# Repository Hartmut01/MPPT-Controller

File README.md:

# MPPT-Controller
#

bla bla bla

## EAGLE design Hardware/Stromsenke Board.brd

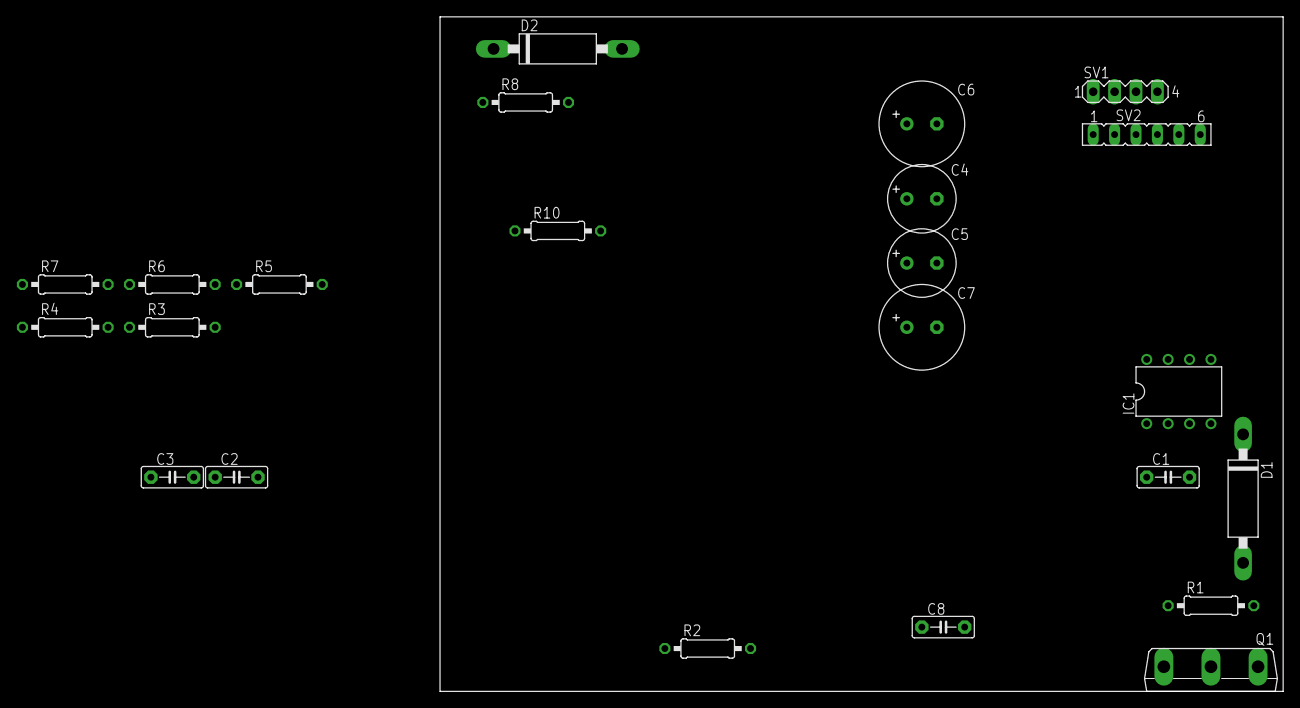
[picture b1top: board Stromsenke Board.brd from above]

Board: 2 copper layers, 100.0 x 80.0 mm, 23 parts (0 on the bottom side), 15 nets, no tracks yet.

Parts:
C1, C2, C3, C8: 100n; C5B2.5
C4, C5: E3,5-8
C6, C7: E3,5-10
D1: 8,7V; C1702-15
D2: 5v; C1702-15
IC1: LM358N; DIL08
Q1: IRFPC40; TO247BV
R1, R7: 1k; 0207/10
R2: 0R1; 0207/10
R3: 2k7; 0207/10
R4: 330R; 0207/10
R5: 10k; 0207/10
R6: 3k3; 0207/10
R8: 670R; 0207/10
R10: 560R; 0207/10
SV1: MA04-1
SV2: FE06

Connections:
GND: C2.1, C4.-, C5.-, C6.-, C7.-, C8.1, D2.A, IC1.4, R2.1, R4.1, R8.2, SV1.1, SV2.1, SV2.5
I_OUT: C3.1, IC1.7
unnamed: D1.A, Q1.G, R1.2
unnamed: IC1.3, R6.1
unnamed: SV1.3, SV2.3
unnamed: C2.2, D2.C, R5.1, SV1.2, SV2.2
unnamed: Q1.S, R1.1, R2.2, R7.2
unnamed: C1.2, D1.C, IC1.1
unnamed: IC1.5, R7.1
unnamed: R3.1, R4.2, R6.2
unnamed: C1.1, IC1.2, R10.1
unnamed: C3.2, IC1.6, R8.1
unnamed: R10.2, SV2.6
unnamed: SV1.4, SV2.4
VCC: C4.+, C5.+, C6.+, C7.+, C8.2, IC1.8, Q1.D, R3.2, R5.2

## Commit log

2018-04-08 Create README.md
    initial commit
2018-04-08 added platform io project
2018-04-09 -Feature EEPROM Wh -Fix Structure
2018-04-13 clean up
2018-04-13 added eeprom class, NOT YET IMPLEMENTED
2018-04-13 trying to fix git ignore
2018-04-13 added library dependencies
2018-04-13 platfrom io setting
2018-04-13 renaming and basic implementation, NOT YET TESTED!
2018-04-13 fix if structure
2018-04-13 unsigned longs instead if signed longs
2018-04-13 fixed formatting
2018-04-13 fixed EEPROM addresses
2018-04-13 added template classes for the display and the MPPT
2018-04-13 -fix EEPROM Safe Problem -feature Hardware switch SMPS
2018-04-14 -fix EEPROM Safe Burden
2018-04-14 -feature Scematics
2018-04-17 Gitignore fix
2018-04-20 initial display class implementation
2018-04-20 config header, meant to be used as configuration file for the MPPT system
2018-04-20 pins header, meant to be used as a container for the pin settings
2018-04-20 fix static field access
2018-04-20 revised eeprom handling: now using struc of display lcd to write in and read from
2018-04-20 introduced data container header which contains a data struct for watt hours and a data struct for the mppt
2018-04-20 gitignore stuff
2018-04-20 added solar panel and controller as data structs
2018-04-20 moved i2c adresses to pins header
2018-04-20 initial ADC implementation
2018-04-20 formatting and comments fix
2018-04-20 added initialize method for pins
2018-04-20 added dac data struct
2018-04-20 added DAC class
2018-04-20 ADC now behaves like a static class
2018-06-16 refactoring finished, testing required!
2018-06-16 update comments
2018-06-17 gitignore update
